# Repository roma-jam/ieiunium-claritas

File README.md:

# Ieiunium Claritas

STM32L + LIS + RGB = Ieiunium Claritas

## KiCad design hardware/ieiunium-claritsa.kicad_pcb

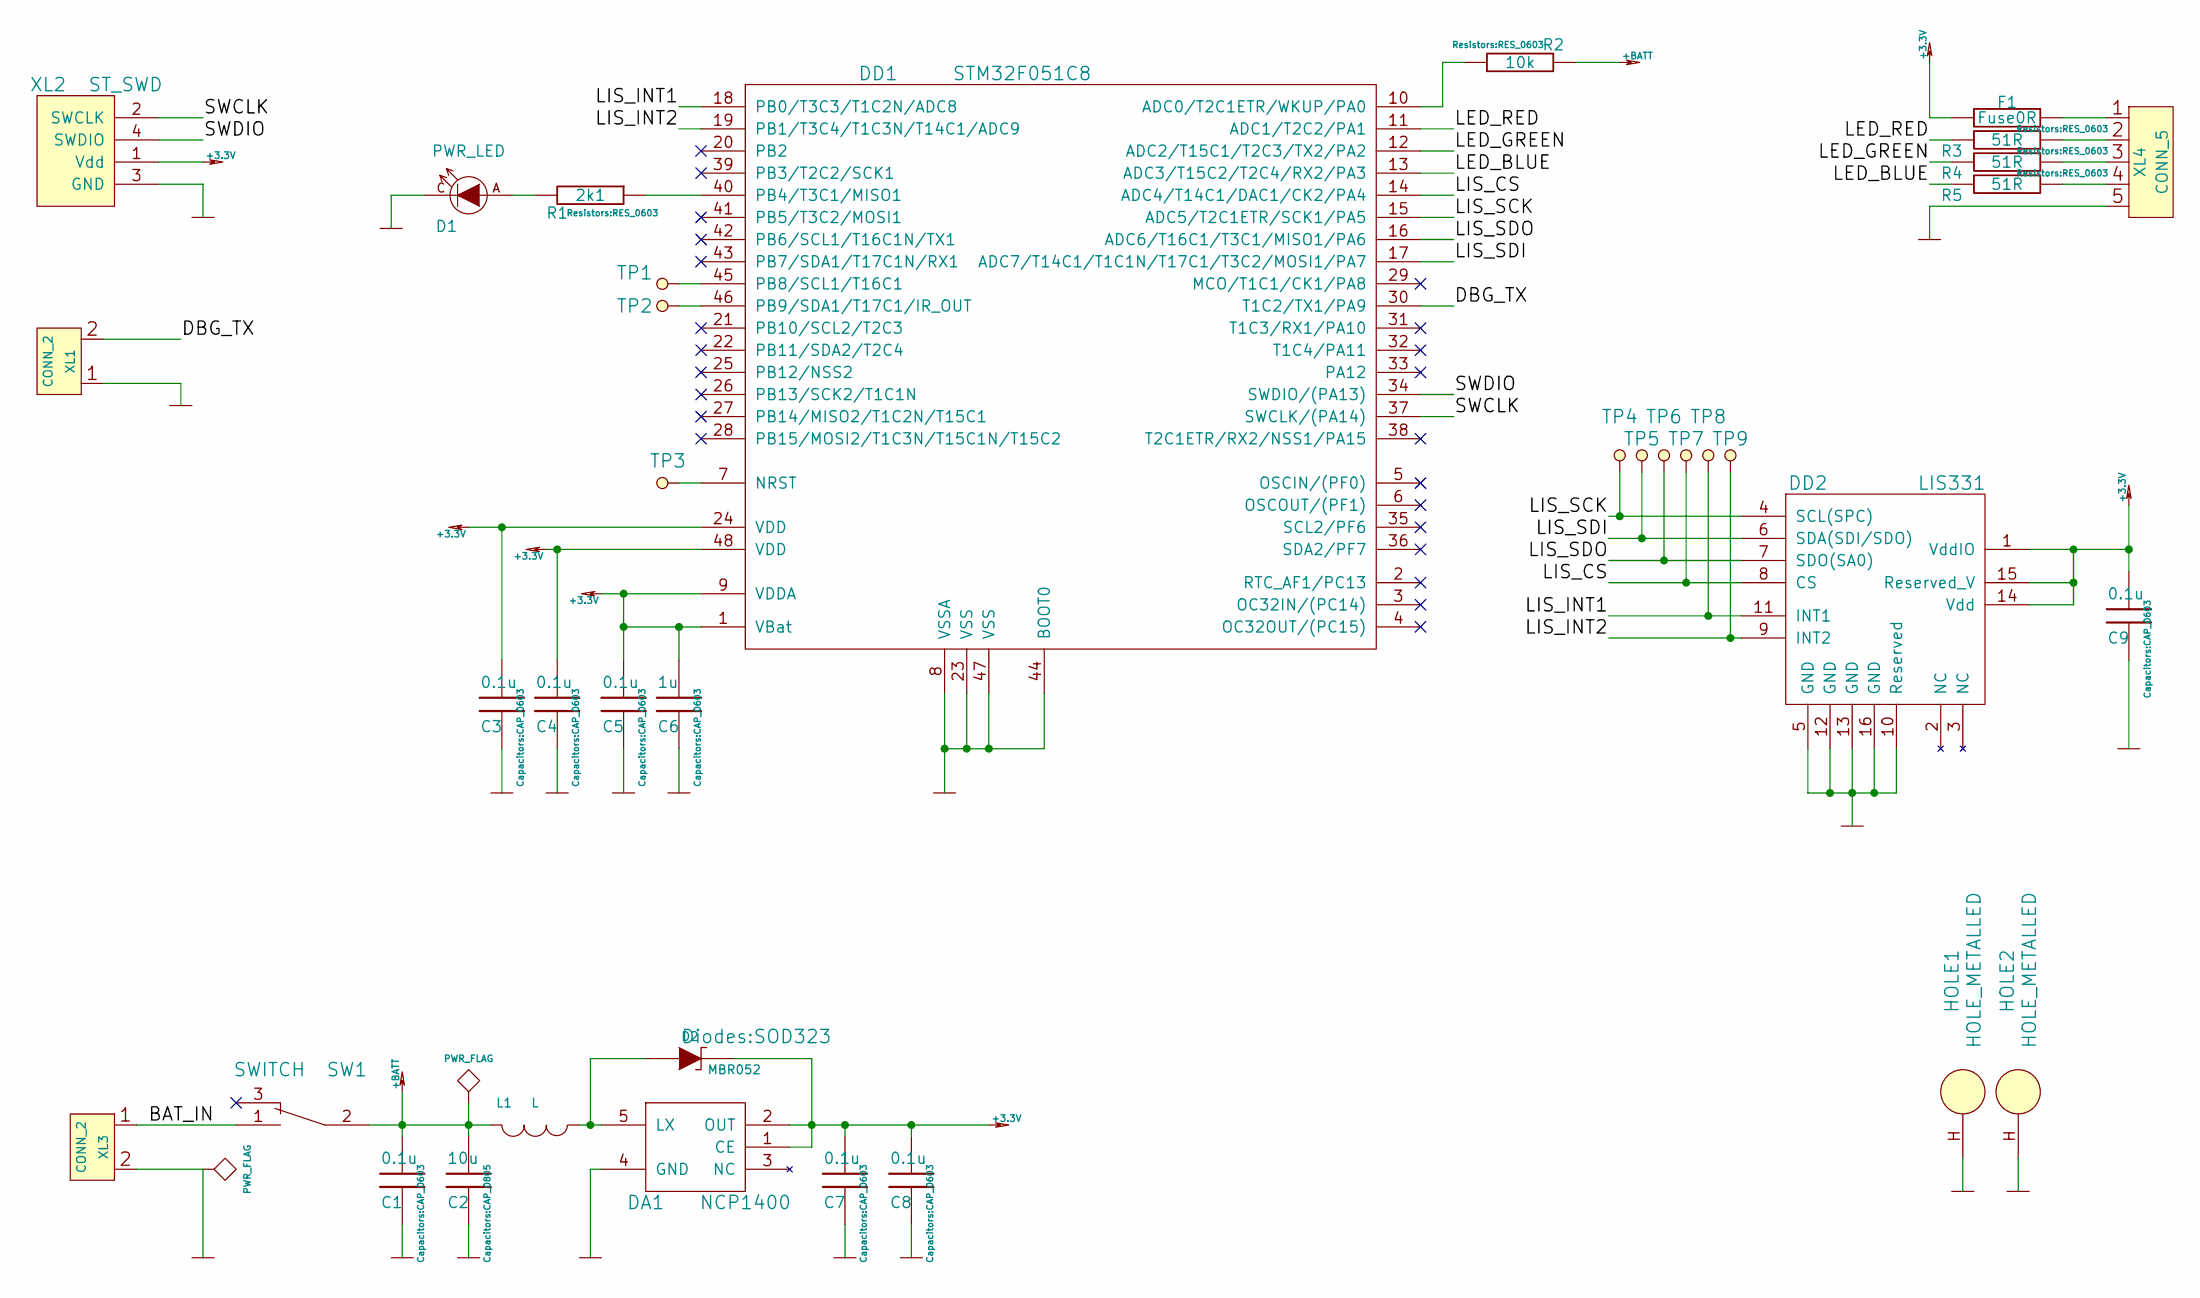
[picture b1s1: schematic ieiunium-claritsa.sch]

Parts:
C1, C3, C4, C5, C7, C8, C9: 0.1u; CAP_0603
C2: 10u; CAP_0805
C6: 1u; CAP_0603
D1: PWR_LED; LED_0603
D2: MBR052; SOD323
DA1: NCP1400; SOT23-5
DD1: STM32F051C8; LQFP48
DD2: LIS331; 16_3X3
F1: Fuse0R; RES_0603_FUSE
HOLE1, HOLE2: HOLE_METALLED; Hole3_5_out6mm
L1: L; CD_type_6.0X5.5
R1: 2k1; RES_0603
R2: 10k; RES_0603
R3, R4, R5: 51R; RES_0603
SW1: SWITCH; Socket_Strip_Straight_1x03_Pitch2.54mm
TP1: SCL; TESTPOINT_1MM
TP2: SDA; TESTPOINT_1MM
TP3: NRST; TESTPOINT_1MM
TP4: SCK; TESTPOINT_1MM
TP5: SDI; TESTPOINT_1MM
TP6: SDO; TESTPOINT_1MM
TP7: CS; TESTPOINT_1MM
TP8: INT1; TESTPOINT_1MM
TP9: INT2; TESTPOINT_1MM
XL1: CONN_2; Socket_Strip_Straight_1x02_Pitch2.54mm
XL2: ST_SWD; Socket_Strip_Straight_1x04_Pitch2.54mm
XL3: CONN_2; BH-6_CR2032
XL4: CONN_5; Socket_Strip_Straight_1x05_Pitch2.54mm

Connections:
+3.3V: C3.1, C4.1, C5.1, C6.1, C7.1, C8.1, C9.1, D2.C, DA1.1 (CE), DA1.2 (OUT), DD1.1 (VBat), DD1.9 (VDDA), DD1.24 (VDD), DD1.48 (VDD), DD2.1 (VddIO), DD2.14 (Vdd), DD2.15 (Reserved_V), F1.2, XL2.1 (Vdd)
+BATT: C1.1, C2.1, L1.2, R2.2, SW1.2
/BAT_IN: SW1.1, XL3.1
/DBG_TX: DD1.30 (T1C2/TX1/PA9), XL1.2 (PM)
/LED_BLUE: DD1.13 (ADC3/T15C2/T2C4/RX2/PA3), R5.2
/LED_GREEN: DD1.12 (ADC2/T15C1/T2C3/TX2/PA2), R4.2
/LED_RED: DD1.11 (ADC1/T2C2/PA1), R3.2
/LIS_CS: DD1.14 (ADC4/T14C1/DAC1/CK2/PA4), DD2.8 (CS), TP7.1
/LIS_INT1: DD1.18 (PB0/T3C3/T1C2N/ADC8), DD2.11 (INT1), TP8.1
/LIS_INT2: DD1.19 (PB1/T3C4/T1C3N/T14C1/ADC9), DD2.9 (INT2), TP9.1
/LIS_SCK: DD1.15 (ADC5/T2C1ETR/SCK1/PA5), DD2.4 (SCL(SPC)), TP4.1
/LIS_SDI: DD1.17 (ADC7/T14C1/T1C1N/T17C1/T3C2/MOSI1/PA7), DD2.6 (SDA(SDI/SDO)), TP5.1
/LIS_SDO: DD1.16 (ADC6/T16C1/T3C1/MISO1/PA6), DD2.7 (SDO(SA0)), TP6.1
/SWCLK: DD1.37 (SWCLK/(PA14)), XL2.2 (SWCLK)
/SWDIO: DD1.34 (SWDIO/(PA13)), XL2.4 (SWDIO)
GND: C1.2, C2.2, C3.2, C4.2, C5.2, C6.2, C7.2, C8.2, C9.2, D1.C, DA1.4 (GND), DD1.8 (VSSA), DD1.23 (VSS), DD1.44 (BOOT0), DD1.47 (VSS), DD2.5 (GND), DD2.10 (Reserved), DD2.12 (GND), DD2.13 (GND), DD2.16 (GND), HOLE1.H, HOLE2.H, XL1.1, XL2.3 (GND), XL3.2 (PM), XL4.5
unnamed: D1.A, R1.2
unnamed: D2.A, DA1.5 (LX), L1.1
unnamed: DD1.7 (NRST), TP3.1
unnamed: DD1.10 (ADC0/T2C1ETR/WKUP/PA0), R2.1
unnamed: DD1.40 (PB4/T3C1/MISO1), R1.1
unnamed: DD1.45 (PB8/SCL1/T16C1), TP1.1
unnamed: DD1.46 (PB9/SDA1/T17C1/IR_OUT), TP2.1
unnamed: F1.1, XL4.1
unnamed: R3.1, XL4.2
unnamed: R4.1, XL4.3
unnamed: R5.1, XL4.4

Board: 2 copper layers, 37 parts (0 on the bottom side), 27 nets, no tracks yet.

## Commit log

2017-05-24 + README.md
2017-05-24 Add hardware project
2017-05-25 Create netlist. Leave switch and L1 without pcb footprints. Await delivery...
2017-05-25 + PCB with footprints
2017-05-26 Proceed PCB
2017-05-29 Increase PCB size
2017-08-02 PCB start
